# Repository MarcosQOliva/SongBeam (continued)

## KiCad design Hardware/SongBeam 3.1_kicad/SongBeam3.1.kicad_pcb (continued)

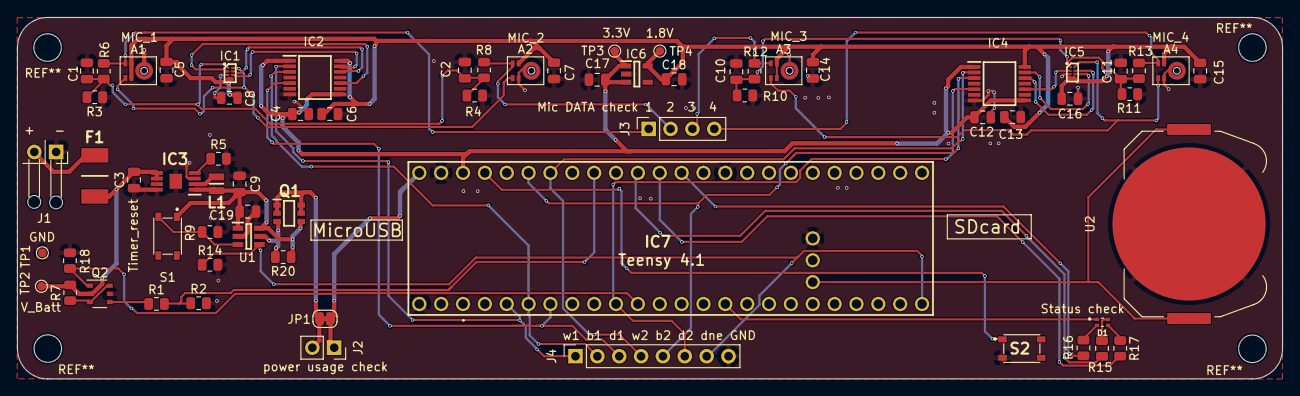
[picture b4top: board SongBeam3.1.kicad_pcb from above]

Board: 2 copper layers, 147.0 x 42.0 mm, 67 parts (0 on the bottom side), 46 nets.

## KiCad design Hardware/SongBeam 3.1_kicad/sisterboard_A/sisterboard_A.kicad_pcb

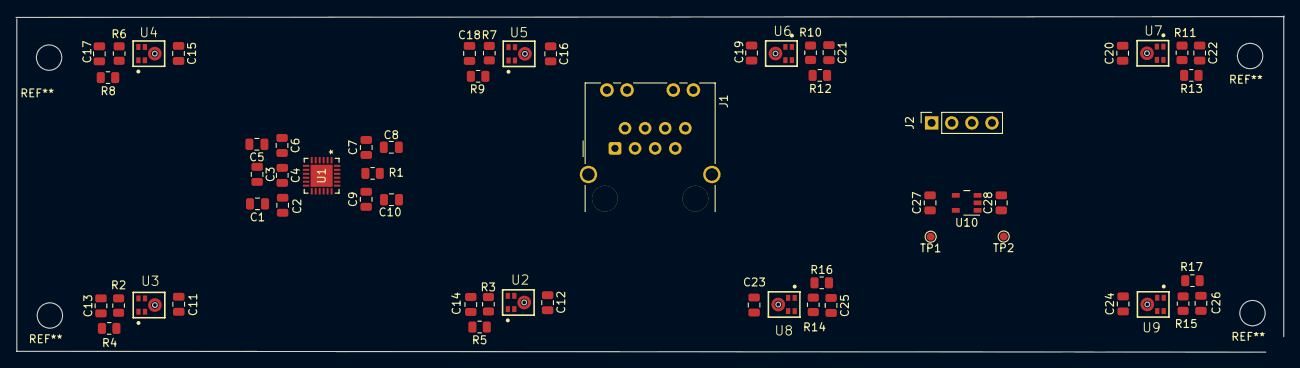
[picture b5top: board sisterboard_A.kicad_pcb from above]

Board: 2 copper layers, 160.2 x 42.5 mm, 59 parts (0 on the bottom side), 25 nets, no tracks yet.

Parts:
C1, C6, C7: 10uF; C_0805_2012Metric
C2, C5, C8, C9, C11, C12, C15, C16, C19, C20, C23, C24: 100nF; C_0805_2012Metric
C3, C4, C10: 1uF; C_0805_2012Metric
C13, C14, C17, C18, C21, C22, C25, C26: 47pF; C_0805_2012Metric
C27, C28: 1µF; C_0805_2012Metric
J1: RJ45; RJ45_Molex_9346520x_Horizontal
J2: Conn_01x04; PinSocket_1x04_P2.54mm_Vertical
R1, R2, R3, R6, R7, R10, R11, R12, R14, R15: 100R; R_0805_2012Metric
R4, R5, R8, R9, R13, R16, R17: 100K; R_0805_2012Metric
TP1, TP2: TestPoint; TestPoint_Pad_D1.0mm
U1: PCMD3180IRTWR
U2, U3, U4, U5, U6, U7, U8, U9: IM66D132H; IFX-PG-TLGA-5N-9-V
U10: LP5907MFX-1.8_NOPB; LP5907MFX-1.2&slash_NOPB

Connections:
+1V8: C1.1, C2.2, C11.1, C12.1, C15.1, C16.1, C19.1, C20.1, C23.1, C24.1, C28.1, TP2.1, U1.1 (AVDD), U2.2 (LR), U2.5 (VDD), U3.5 (VDD), U4.2 (LR), U4.5 (VDD), U5.5 (VDD), U6.2 (LR), U6.5 (VDD), U7.5 (VDD), U8.2 (LR), U8.5 (VDD), U9.5 (VDD), U10.5 (OUT)
+3.3V: C9.1, C10.2, C27.2, J1.7, TP1.1, U1.19 (IOVDD), U10.1 (IN), U10.3 (EN)
/BCLK: J1.2, U1.22 (BCLK)
/SCL_MOSI: J1.5, U1.17 (SCL_MOSI)
/SDA_SSZ: J1.4, U1.18 (SDA_SSZ)
/SDOUT: J1.3, R1.1
/SHDNZ: J1.6, U1.14 (SHDNZ)
GND: C1.2, C2.1, C3.2, C4.2, C5.1, C6.2, C7.1, C8.2, C9.2, C10.1, C11.2, C12.2, C13.2, C14.2, C15.2, C16.2, C17.2, C18.2, C19.2, C20.2, C21.2, C22.2, C23.2, C24.2, C25.2, C26.2, C27.1, C28.2, J1.8, R4.2, R5.2, R8.2, R9.2, R12.1, R13.2, R16.2, R17.2, U1.4 (AVSS), U1.15 (ADDR1_MISO), U1.16 (ADDR0_SCLK), U1.25 (VSS), U2.3 (GND), U3.2 (LR), U3.3 (GND), U4.3 (GND), U5.2 (LR), U5.3 (GND), U6.3 (GND), U7.2 (LR), U7.3 (GND), U8.3 (GND), U9.2 (LR), U9.3 (GND), U10.2 (GND)
unnamed: J2.1, R10.1, R11.1, U6.1 (DATA), U7.1 (DATA)
unnamed: J2.2, R6.1, R7.1, U4.1 (DATA), U5.1 (DATA)
unnamed: J2.3, R2.1, R3.1, U2.1 (DATA), U3.1 (DATA)
unnamed: J2.4, R14.2, R15.2, U8.1 (DATA), U9.1 (DATA)
unnamed: C5.2, C6.1, U1.2 (AREG)
unnamed: C7.2, C8.1, U1.24 (DREG)
unnamed: C4.1, U1.5 (MICBIAS)
unnamed: U1.11 (PDMCLK3_GPO3), U2.4 (CLK), U3.4 (CLK)
unnamed: U1.13 (PDMCLK4_GPO4), U8.4 (CLK), U9.4 (CLK)
unnamed: C21.1, C22.1, R10.2, R11.2, R12.2, R13.1, U1.6 (PDMDIN1_GPI1)
unnamed: C17.1, C18.1, R6.2, R7.2, R8.1, R9.1, U1.8 (PDMDIN2_GPI2)
unnamed: C13.1, C14.1, R2.2, R3.2, R4.1, R5.1, U1.10 (PDMDIN3_GPI3)
unnamed: C25.1, C26.1, R14.1, R15.1, R16.1, R17.1, U1.12 (PDMDIN4_GPI4)
unnamed: U1.7 (PDMLK1_GPO1), U6.4 (CLK), U7.4 (CLK)
unnamed: U1.9 (PDMLK2_GPO2), U4.4 (CLK), U5.4 (CLK)
unnamed: R1.2, U1.21 (SDOUT)
unnamed: C3.1, U1.3 (VREF)

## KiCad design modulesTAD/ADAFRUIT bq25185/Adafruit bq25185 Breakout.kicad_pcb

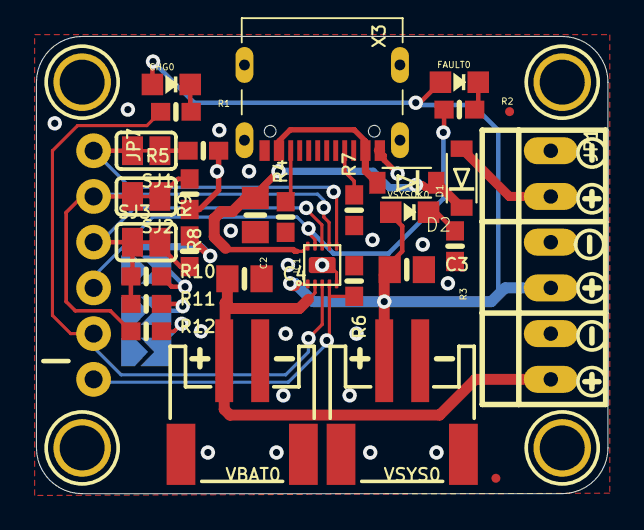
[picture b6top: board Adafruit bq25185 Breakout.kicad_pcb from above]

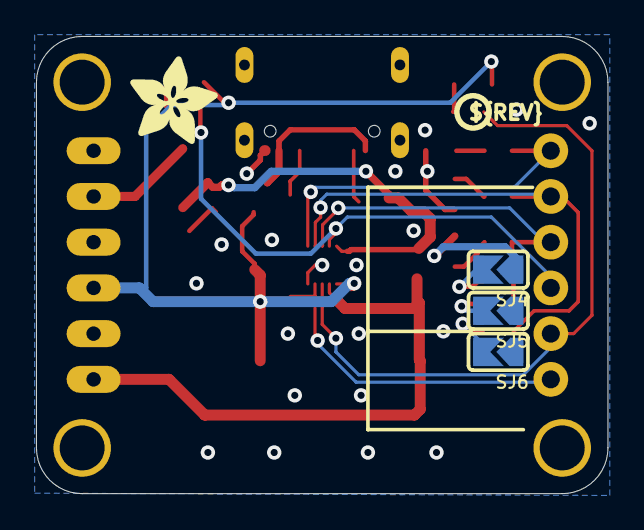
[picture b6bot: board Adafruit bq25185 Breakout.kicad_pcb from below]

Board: 2 copper layers, 31.8 x 25.4 mm, 69 parts (13 on the bottom side), 23 nets.

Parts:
C2, C3, C4: 22uF; 0805-NO
CHG0: ORANGE; CHIPLED_0805_NOOUTLINE
D1, D2: MBRX120; SOD-123FL
FAULT0: RED; CHIPLED_0805_NOOUTLINE
IC1: BQ25185; WSON10
JP1: 1X06_OVALWAVE
JP2, JP4: FIDUCIAL1.5X3; FIDUCIAL_0.5MM
JP7: 1X06_ROUND_76
PLABEL0: PLABEL0
PLABEL1: PLABEL1
PLABEL2: PLABEL2
PLABEL3: PLABEL3
PLABEL4: PLABEL4
PLABEL5: PLABEL5
PLABEL6: PLABEL6
PLABEL7: PLABEL7
PLABEL8: PLABEL8
PLABEL9: PLABEL9
PLABEL10: PLABEL10
PLABEL11: PLABEL11
PLABEL12: PLABEL12
PLABEL13: PLABEL13
PLABEL14: PLABEL14
PLABEL15: PLABEL15
PLABEL16: PLABEL16
PLABEL17: PLABEL17
PLABEL18: PLABEL18
PLABEL19: PLABEL19
PLABEL20: PLABEL20
PLABEL21: PLABEL21
PLABEL22: PLABEL22
R1, R2, R3: 1K; 0603-NO
R4, R7, R12: 5.1K; 0603-NO
R5, R6: 10K; 0603-NO
R8: 13K; 0603-NO
R9: 600; 0603-NO
R10: 300; 0603-NO
R11: 1200; 0603-NO
SJ1, SJ2, SJ3: SOLDERJUMPER_CLOSEDWIRE
SJ4, SJ5, SJ6: SOLDERJUMPER_ARROW_NOPASTE
U$11, U$16, U$18, U$19: MOUNTINGHOLE2.5; MOUNTINGHOLE_2.5_PLATED
U$23, U$27, U$28: SYMBOL_PLUS
U$24, U$25, U$26: SYMBOL_MINUS
U$46: ADAFRUIT_5MM
U$47: PCBFEAT-REV-040
VBAT0: JST2PH; JSTPH2_BATT
VSYS0: JST2PH; JSTPH2_BATT
VSYSOK0: GREEN; CHIPLED_0805_NOOUTLINE
X3: USBC; USB_C_CUSB31-CFM2AX-01-X

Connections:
5.0V: C3.1, CHG0.A, FAULT0.A, IC1.1, JP1.4, VSYS0.2, VSYSOK0.A
/CE: IC1.4, JP7.6, R6.2
GND: C2.2, C3.2, C4.2, IC1.5, IC1.PAD, JP1.1, JP1.3, JP1.5, R3.2, R4.1, R5.1, R6.1, R7.1, R8.2, R9.2, SJ4.1, SJ5.1, SJ6.1, VBAT0.1, VBAT0.NC1, VBAT0.NC2, VSYS0.1, VSYS0.NC1, VSYS0.NC2, X3.A1B12, X3.B1A12
ISET: IC1.8, JP7.3, R10.1, R11.1, SJ3.1
unnamed: CHG0.C, R1.2
unnamed: FAULT0.C, R2.2
unnamed: R8.1, SJ2.1
unnamed: R4.2, X3.B5
unnamed: R5.2, SJ1.1
unnamed: R7.2, X3.A5
unnamed: R9.1, SJ3.2
unnamed: R10.2, SJ4.2
unnamed: R11.2, SJ5.2
unnamed: R12.2, SJ6.2
unnamed: D1.A, JP1.2
unnamed: R3.1, VSYSOK0.C
STAT1: IC1.9, JP7.4, R2.1
STAT2: IC1.3, JP7.5, R1.1
THERM: IC1.6, JP7.1, SJ1.2
USB: D2.A, X3.A4B9, X3.B4A9
VBAT: C4.1, IC1.2, JP1.6, VBAT0.2
VBUS: C2.1, D1.C, D2.C, IC1.10
VSET: IC1.7, JP7.2, R12.1, SJ2.2

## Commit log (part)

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2026-01-19 daughterBRD-UPDATE main BRD
    added a full desing for daugther BRD, has a new microcontroller for 8 mics with TDM output
    Start changes in the 4.0 version of the Soundbeam, making combatible with the daughter board
2026-01-21 tweaks in daugtherboard and develop in the main 4.0 board
    changed voltage, added voltage translators and swiched from ethernet to HDMI
2026-01-22 Small tweaks, implementing the power modules
2026-01-26 small tweaks
2026-01-29 tweaks better
2026-02-03 backup switch to cat6
2026-02-07 V1 BRD_4.0
    finish the schematics
2026-02-10 pcb sketch v1
2026-02-11 pcb savepoint
2026-02-11 prerouting
2026-02-11 Tracing V1 SB4.0
2026-02-12 Pcb bugfixxing
2026-02-12 debugging
2026-02-12 debug
2026-02-15 debuggin done
2026-02-16 gerber
2026-02-26 Layout updates
2026-02-26 makeover director + pcb layout finish
2026-02-26 tweak bom
2026-03-02 4.1.1
2026-03-03 bom main board update
2026-03-03 change resistor 300 to 300R
2026-03-03 bom fix
2026-03-03 fixed weird bug that keeps deleting microphone
2026-03-03 fixed the bom too from the bug
2026-03-04 added a version for manual routing
2026-04-28 sanity push
2026-04-28 ethernet port updated, fixed flaws 1.1 DB
2026-04-28 implemented ethernet port pcb R/a
